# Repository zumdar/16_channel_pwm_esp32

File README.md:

# 16 Channel PWM led dimming board for ESP32

this repo contains the files for a 16 channel pcb to dim LEDS. 

## Description

I designed this board originally for my friend [Eddie Farr](https://www.instagram.com/freaughouse/?hl=en) for an led sculpture he is working on. I've also wanted something like this for a while to dim analog LED strips easily via WLED or ArtNet, or just plain old locally from a microcontroller.

It is designed to take in voltages from 5 to 37 Volts to power the ESP32. That way you can use this with 12 or 24 volt LEDs and dont have to deal with an extra 5V power supply to power the esp32. 

There are two separate places to put power in. 
EITHER plug 5V into the 5V side, or plug 7 - 37V into the other side. 
## pinout

LED1 = GPIO 5

LED2 = GPIO 12

LED3 = GPIO 13

LED4 = GPIO 14

LED5 = GPIO 15

LED6 = GPIO 16

LED7 = GPIO 17

LED8 = GPIO 18

LED9 = GPIO 19

LED10 = GPIO 21

LED11 = GPIO 22

LED12 = GPIO 23

LED13 = GPIO 25

LED14 = GPIO 26

LED15 = GPIO 27

LED16 = GPIO 32
## Schematic 
Rev 3

Rev 1 

## PCB

Rev. 3 - pcb with larger transistors and larger connectors:

Rev. 1 - pcb with larger transistors:

Rev. 1 - pcb with smaller transistors:

## Parts references
### Connectors
- On version 1.3 we are trying out some Molex Microfit connectors
- Crimping tool - [Engineer PA09](https://www.amazon.com/ENGINEER-AWG32-AWG20-Connectors-Oil-Resistant-PA-09/dp/B002AVVO7K?th=1) 
- 
### Common parts
- [Mouser Cart](https://www.mouser.com/ProjectManager/ProjectDetail.aspx?AccessID=f114f2123e) for QTY 5 REV2 boards - this is parts not included with the JLCPCB assembly. 

- [Recommended Generic Crimper](https://www.amazon.com/ENGINEER-AWG32-AWG20-Connectors-Oil-Resistant-PA-09/dp/B002AVVO7K) for Molex Microfit Connectors

- using ESP-WROOM-32 dev board. 2.05" x 1.18" like the kind [found here](https://www.amazon.com/ESP-WROOM-32-Development-Microcontroller-Integrated-Compatible/dp/B0BK13HWBJ/ref=sr_1_4?keywords=esp32&qid=1679947379&sr=8-4&th=1)
- Both pcbs mount with M3 screws
- board has two places for power. one for 5V and one for 8V - 40V. The two connectors MSTBV/MSTBA Phoenix Type, 5.08 pitch. 
  - straight receptacle/header: [1747993 (green)](https://www.mouser.com/ProductDetail/Phoenix-Contact/1747993?qs=cq3Rj917t3li0%2FrJTXaRgg%3D%3D) or [1836561 (orange)](https://www.mouser.com/ProductDetail/Phoenix-Contact/1836561?qs=RahONj4mt5imYCprRrL9IA%3D%3D) or [1740893 (black)](https://www.mouser.com/ProductDetail/Phoenix-Contact/1740893?qs=o3rrLWFGhRnNm6PoJeAVCw%3D%3D)
  - right angle receptacle/header: [1736036 (green)](https://www.mouser.com/ProductDetail/Phoenix-Contact/1736036?qs=IGPQaF7TU6v9VVAvkUDQlA%3D%3D) or [1702878 (white)](https://www.mouser.com/ProductDetail/Phoenix-Contact/1702878?qs=2WS7V4AoKFqZwxKPPB6GZw%3D%3D) or [1876848 (orange)](https://www.mouser.com/ProductDetail/Phoenix-Contact/1876848?qs=KDxjV83btlSGzDlv5NRfLA%3D%3D)
  - terminal block plug: [Wurth 691351500002](https://www.mouser.com/ProductDetail/Wurth-Elektronik/691351500002?qs=7gQLVZk5cPkg%2FrpRGyiXgA%3D%3D) or [Kobiconn 158-P022ESDVP-E](https://www.mouser.com/ProductDetail/Kobiconn/158-P022ESDVP-E?qs=EibfsPFbZarDIylQPyTRxA%3D%3D) or [Amphenol TJ0251530000G](https://www.mouser.com/ProductDetail/Amphenol-Anytek/TJ0251530000G?qs=Mv7BduZupUjx%252Becl1KCPZg%3D%3D)
### larger pcb
- Enclosure mounts with #8 wood screws
-  the larger board uses 3.81mm pitch connector for led outputs
   - 16 channel plug -  pluggable screw terminal block - [TBP02P1-381-16BE](https://www.mouser.com/ProductDetail/490-TBP02P1-381-16BE) 
   - screw terminal receptacle/header 
[TBP02R1-381-16BE](https://www.mouser.com/ProductDetail/490-TBP02R1-381-16BE)
### smaller pcb
- smaller board uses 2.54mm connector for led outputs

## Help

Any advise for common problems or issues.

## Authors

[william kennedy](https://freakylamps.com/)

## Version History

* 1.0
    * Initial Release - March 15, 2023
* 1.1
    * new design with larger TO-252 package for NMOS - March 20, 2023
* 1.2 - april 5, 2023
  * v2 of smaller board. v1 had NMOS pinout wrong
* Rev 3 - May 22, 2024
  * large boards are now larger, using MicroFit connectors for the led outputs, terminal block for PSU inputs
  * switch is on front now
  * Q17 had pinout wrong

## License

This project is licensed under the [NAME HERE] License - see the LICENSE.md file for details

## Acknowledgments

Inspiration comes from [quinLED's analog boards](https://quinled.info/quinled-an-quad/)

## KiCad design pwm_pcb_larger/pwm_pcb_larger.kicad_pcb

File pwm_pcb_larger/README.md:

# 16 Channel PWM led dimming board for ESP32 - larger version with TO252 package

this repo contains the files for a 16 channel pcb to dim leds using TO-252 NMOS package for more current. 

## use case 
- WLED to dim analog LED strips
- ArtNet dmx over wifi to the ESP32 to control 16 channels of led wirelessly

## Author

[william kennedy](https://freakylamps.com/)

## Version History

* 1.1
    * Initial Release - March 20, 2023

## License

This project is licensed under the [NAME HERE] License - see the LICENSE.md file for details

## Acknowledgments

Inspiration comes from [quinLED's analog boards](https://quinled.info/quinled-an-quad/)

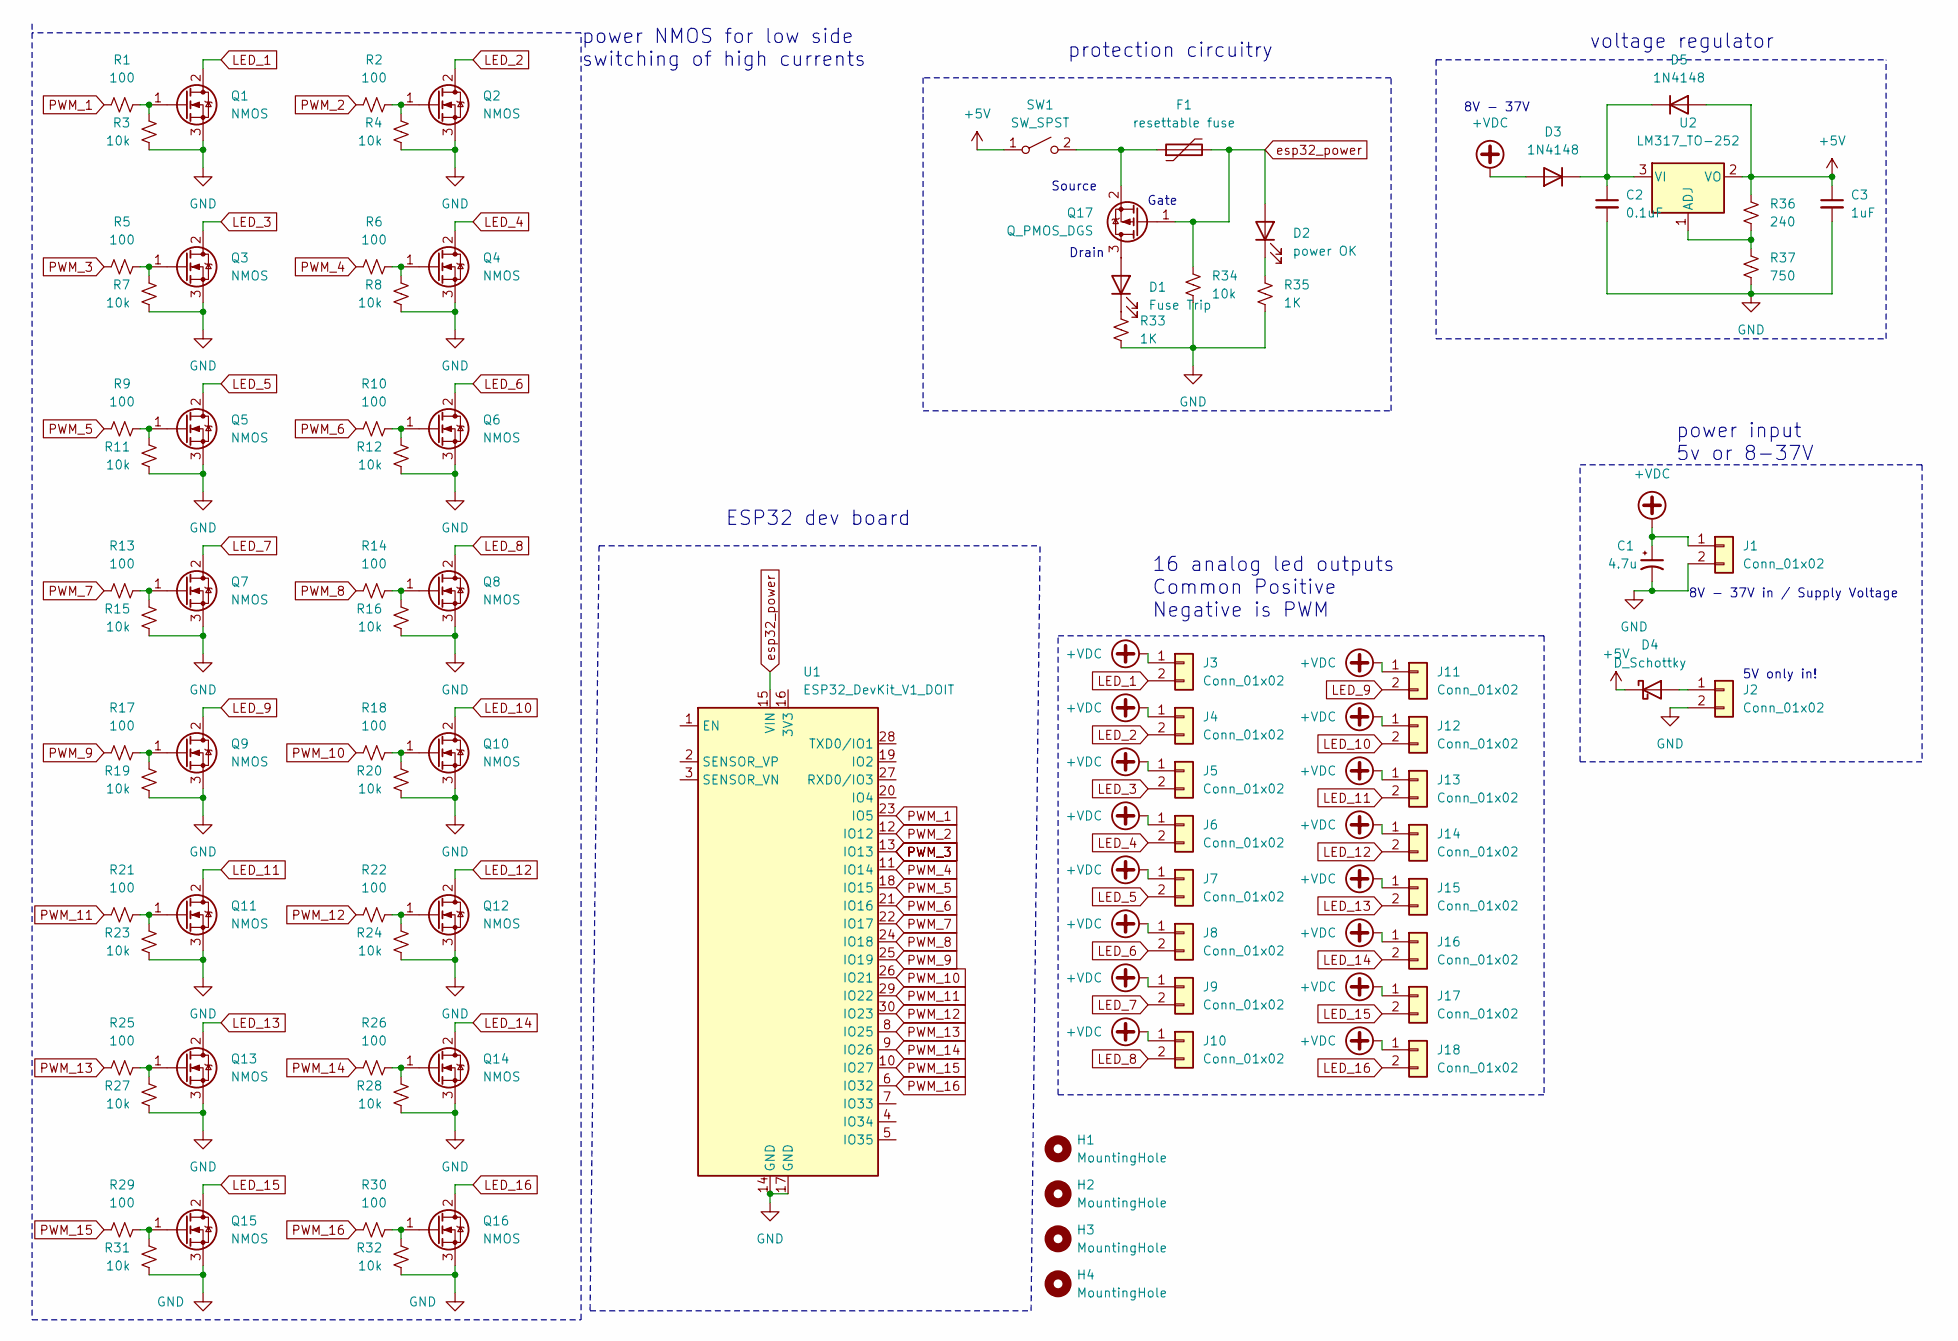
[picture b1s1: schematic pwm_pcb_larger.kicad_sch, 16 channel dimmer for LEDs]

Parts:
C1: 4.7u; C_1206_3216Metric_Pad1.33x1.80mm_HandSolder; LCSC C29823
C2: 0.1uF; C_1206_3216Metric_Pad1.33x1.80mm_HandSolder; LCSC C24497
C3: 1uF; C_1206_3216Metric_Pad1.33x1.80mm_HandSolder; LCSC C1848
D1: Fuse Trip; LED_0805_2012Metric; LCSC C84256
D2: power OK; LED_0805_2012Metric; LCSC C34499
D3, D5: 1N4148; D_SOD-323; LCSC C2128
D4: D_Schottky; D_SMA; LCSC C2480
F1: resettable fuse; Fuse_1206_3216Metric; LCSC C70077
H1, H2, H3, H4: MountingHole; MountingHole_3.2mm_M3
J1, J2: Conn_01x02; Kobiconn - 2 pin terminal - 158P02DT39BE
J3, J4, J5, J6, J7, J8, J9, J10, J11, J12, J13, J14, J15, J16, J17, J18: Conn_01x02; Molex_Micro-Fit_3.0_43045-0212_2x01_P3.00mm_Vertical
Q1, Q2, Q3, Q4, Q5, Q6, Q7, Q8, Q9, Q10, Q11, Q12, Q13, Q14, Q15, Q16: NMOS; TO-252-2; LCSC C2995345
Q17: Q_PMOS_DGS; SOT-23; LCSC C15127
R1, R2, R5, R6, R9, R10, R13, R14, R17, R18, R21, R22, R25, R26, R29, R30: 100; R_0805_2012Metric; LCSC C17408
R3, R4, R7, R8, R11, R12, R15, R16, R19, R20, R23, R24, R27, R28, R31, R32, R34: 10k; R_0805_2012Metric; LCSC C17414
R33, R35: 1K; R_0805_2012Metric; LCSC C17513
R36: 240; R_0805_2012Metric; LCSC C17572
R37: 750; R_0805_2012Metric; LCSC C17818
SW1: SW_SPST; SW_SPST_CK_RS282G05A3; LCSC C54948
U1: ESP32_DevKit_V1_DOIT; esp32_devkit_v1_doit
U2: LM317_TO-252; TO-252-2; LCSC C75510

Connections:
+5V: C3.1, D4.1 (K), D5.2 (A), R36.1, SW1.1 (A), U2.2 (VO)
+VDC: C1.1, D3.2 (A), J1.1, J3.1, J4.1, J5.1, J6.1, J7.1, J8.1, J9.1, J10.1, J11.1, J12.1, J13.1, J14.1, J15.1, J16.1, J17.1, J18.1
GND: C1.2, C2.2, C3.2, J1.2, J2.2, Q1.3 (S), Q2.3 (S), Q3.3 (S), Q4.3 (S), Q5.3 (S), Q6.3 (S), Q7.3 (S), Q8.3 (S), Q9.3 (S), Q10.3 (S), Q11.3 (S), Q12.3 (S), Q13.3 (S), Q14.3 (S), Q15.3 (S), Q16.3 (S), R3.1, R4.1, R7.1, R8.1, R11.1, R12.1, R15.1, R16.1, R19.1, R20.1, R23.1, R24.1, R27.1, R28.1, R31.1, R32.1, R33.1, R34.1, R35.1, R37.2, U1.14 (GND), U1.17 (GND)
LED_1: J3.2, Q1.2 (D)
LED_2: J4.2, Q2.2 (D)
LED_3: J5.2, Q3.2 (D)
LED_4: J6.2, Q4.2 (D)
LED_5: J7.2, Q5.2 (D)
LED_6: J8.2, Q6.2 (D)
LED_7: J9.2, Q7.2 (D)
LED_8: J10.2, Q8.2 (D)
LED_9: J11.2, Q9.2 (D)
LED_10: J12.2, Q10.2 (D)
LED_11: J13.2, Q11.2 (D)
LED_12: J14.2, Q12.2 (D)
LED_13: J15.2, Q13.2 (D)
LED_14: J16.2, Q14.2 (D)
LED_15: J17.2, Q15.2 (D)
LED_16: J18.2, Q16.2 (D)
unnamed: D1.2 (A), Q17.3 (D)
unnamed: D1.1 (K), R33.2
unnamed: D2.1 (K), R35.2
unnamed: C2.1, D3.1 (K), D5.1 (K), U2.3 (VI)
unnamed: D4.2 (A), J2.1
unnamed: Q1.1 (G), R1.2, R3.2
unnamed: Q2.1 (G), R2.2, R4.2
unnamed: Q3.1 (G), R5.2, R7.2
unnamed: Q4.1 (G), R6.2, R8.2
unnamed: Q5.1 (G), R9.2, R11.2
unnamed: Q6.1 (G), R10.2, R12.2
unnamed: Q7.1 (G), R13.2, R15.2
unnamed: Q8.1 (G), R14.2, R16.2
unnamed: Q9.1 (G), R17.2, R19.2
unnamed: Q10.1 (G), R18.2, R20.2
unnamed: Q11.1 (G), R21.2, R23.2
unnamed: Q12.1 (G), R22.2, R24.2
unnamed: Q13.1 (G), R25.2, R27.2
unnamed: Q14.1 (G), R26.2, R28.2
unnamed: Q15.1 (G), R29.2, R31.2
unnamed: Q16.1 (G), R30.2, R32.2
unnamed: F1.1, Q17.2 (S), SW1.2 (B)
unnamed: R36.2, R37.1, U2.1 (ADJ)
PWM_1: R1.1, U1.23 (IO5)
PWM_2: R2.1, U1.12 (IO12)
PWM_3: R5.1, U1.13 (IO13)
PWM_4: R6.1, U1.11 (IO14)
PWM_5: R9.1, U1.18 (IO15)
PWM_6: R10.1, U1.21 (IO16)
PWM_7: R13.1, U1.22 (IO17)
PWM_8: R14.1, U1.24 (IO18)
PWM_9: R17.1, U1.25 (IO19)
PWM_10: R18.1, U1.26 (IO21)
PWM_11: R21.1, U1.29 (IO22)
PWM_12: R22.1, U1.30 (IO23)
PWM_13: R25.1, U1.8 (IO25)
PWM_14: R26.1, U1.9 (IO26)
PWM_15: R29.1, U1.10 (IO27)
PWM_16: R30.1, U1.6 (IO32)
esp32_power: D2.2 (A), F1.2, Q17.1 (G), R34.2, U1.15 (VIN)

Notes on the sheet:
5V only in!
power NMOS for low side switching of high currents
ESP32 dev board
Source
Drain
8V - 37V
8V - 37V in / Supply Voltage
power input 5v or 8-37V
Gate
protection circuitry
voltage regulator
16 analog led outputs Common Positive Negative is PWM

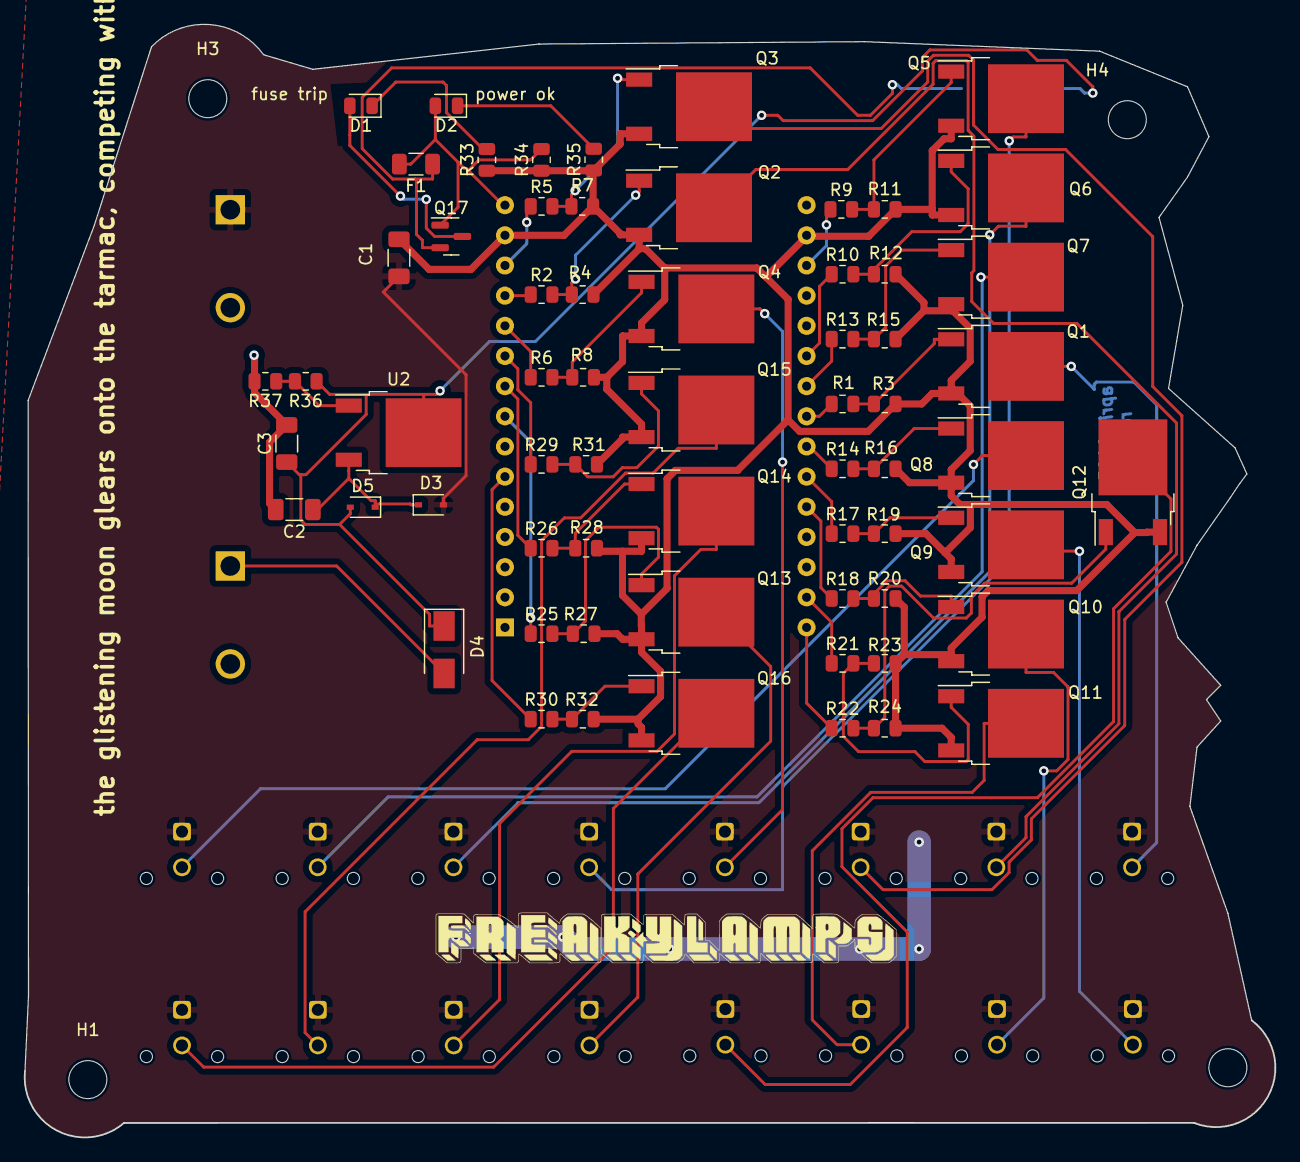
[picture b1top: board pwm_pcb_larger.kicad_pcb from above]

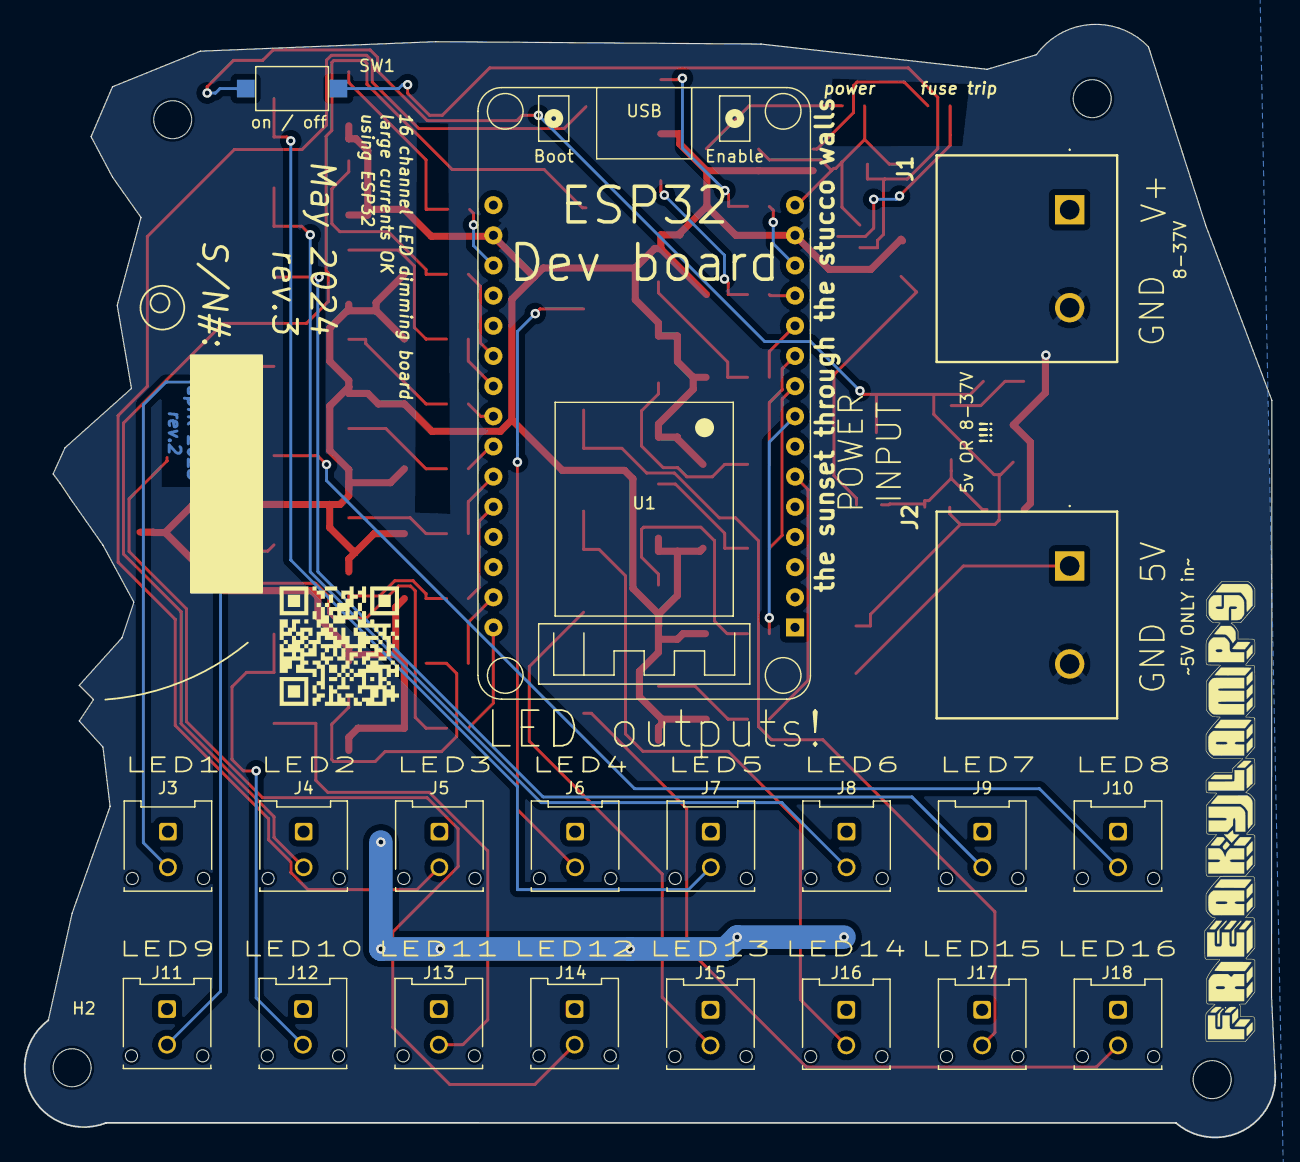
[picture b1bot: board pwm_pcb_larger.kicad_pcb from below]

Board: 2 copper layers, 105.3 x 93.7 mm, 89 parts (21 on the bottom side), 59 nets.

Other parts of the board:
G1: LOGO; 16_channel_pcb

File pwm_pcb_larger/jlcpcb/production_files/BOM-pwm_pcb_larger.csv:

Comment,Designator,Footprint,LCSC
Q_PMOS_DGS,Q17,SOT-23,C15127
100,"R1,R10,R13,R14,R17,R18,R2,R21,R22,R25,R26,R29,R30,R5,R6,R9",R_0805_2012Metric,C17408
10k,"R11,R12,R15,R16,R19,R20,R23,R24,R27,R28,R3,R31,R32,R34,R4,R7,R8",R_0805_2012Metric,C17414
1K,"R33,R35",R_0805_2012Metric,C17513
240,R36,R_0805_2012Metric,C17572
750,R37,R_0805_2012Metric,C17818
1uF,C3,C_1206_3216Metric_Pad1.33x1.80mm_HandSolder,C1848
1N4148,"D3,D5",D_SOD-323,C2128
0.1uF,C2,C_1206_3216Metric_Pad1.33x1.80mm_HandSolder,C24497
D_Schottky,D4,D_SMA,C2480
4.7u,C1,C_1206_3216Metric_Pad1.33x1.80mm_HandSolder,C29823
NMOS,"Q1,Q10,Q11,Q12,Q13,Q14,Q15,Q16,Q2,Q3,Q4,Q5,Q6,Q7,Q8,Q9",TO-252-2,C2995345
power OK,D2,LED_0805_2012Metric,C34499
SW_SPST,SW1,SW_SPST_CK_RS282G05A3,C54948
resettable fuse,F1,Fuse_1206_3216Metric,C70077
LM317_TO-252,U2,TO-252-2,C75510
Fuse Trip,D1,LED_0805_2012Metric,C84256
Conn_01x02,J3,Molex_Micro-Fit_3.0_43045-0212_2x01_P3.00mm_Vertical,
Conn_01x02,J2,Kobiconn - 2 pin terminal - 158P02DT39BE,
Conn_01x02,J1,Kobiconn - 2 pin terminal - 158P02DT39BE,
ESP32_DevKit_V1_DOIT,U1,esp32_devkit_v1_doit,
Conn_01x02,J9,Molex_Micro-Fit_3.0_43045-0212_2x01_P3.00mm_Vertical,
Conn_01x02,J13,Molex_Micro-Fit_3.0_43045-0212_2x01_P3.00mm_Vertical,
Conn_01x02,J4,Molex_Micro-Fit_3.0_43045-0212_2x01_P3.00mm_Vertical,
Conn_01x02,J15,Molex_Micro-Fit_3.0_43045-0212_2x01_P3.00mm_Vertical,
Conn_01x02,J6,Molex_Micro-Fit_3.0_43045-0212_2x01_P3.00mm_Vertical,
Conn_01x02,J11,Molex_Micro-Fit_3.0_43045-0212_2x01_P3.00mm_Vertical,
Conn_01x02,J17,Molex_Micro-Fit_3.0_43045-0212_2x01_P3.00mm_Vertical,
Conn_01x02,J14,Molex_Micro-Fit_3.0_43045-0212_2x01_P3.00mm_Vertical,
Conn_01x02,J12,Molex_Micro-Fit_3.0_43045-0212_2x01_P3.00mm_Vertical,
Conn_01x02,J8,Molex_Micro-Fit_3.0_43045-0212_2x01_P3.00mm_Vertical,
Conn_01x02,J7,Molex_Micro-Fit_3.0_43045-0212_2x01_P3.00mm_Vertical,
Conn_01x02,J10,Molex_Micro-Fit_3.0_43045-0212_2x01_P3.00mm_Vertical,
Conn_01x02,J18,Molex_Micro-Fit_3.0_43045-0212_2x01_P3.00mm_Vertical,
Conn_01x02,J16,Molex_Micro-Fit_3.0_43045-0212_2x01_P3.00mm_Vertical,
Conn_01x02,J5,Molex_Micro-Fit_3.0_43045-0212_2x01_P3.00mm_Vertical,

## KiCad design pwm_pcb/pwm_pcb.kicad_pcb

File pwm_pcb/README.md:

# 16 Channel PWM led dimming board for ESP32

this repo contains the files for a 16 channel pcb to dim leds. 

## Description

An in-depth paragraph about your project and overview of use.

## Getting Started

## Help

Any advise for common problems or issues.

## Authors

[william kennedy](https://freakylamps.com/)

## Version History

* 1.0
    * Initial Release - March 15, 2023

## License

This project is licensed under the [NAME HERE] License - see the LICENSE.md file for details

## Acknowledgments

Inspiration, code snippets, etc.

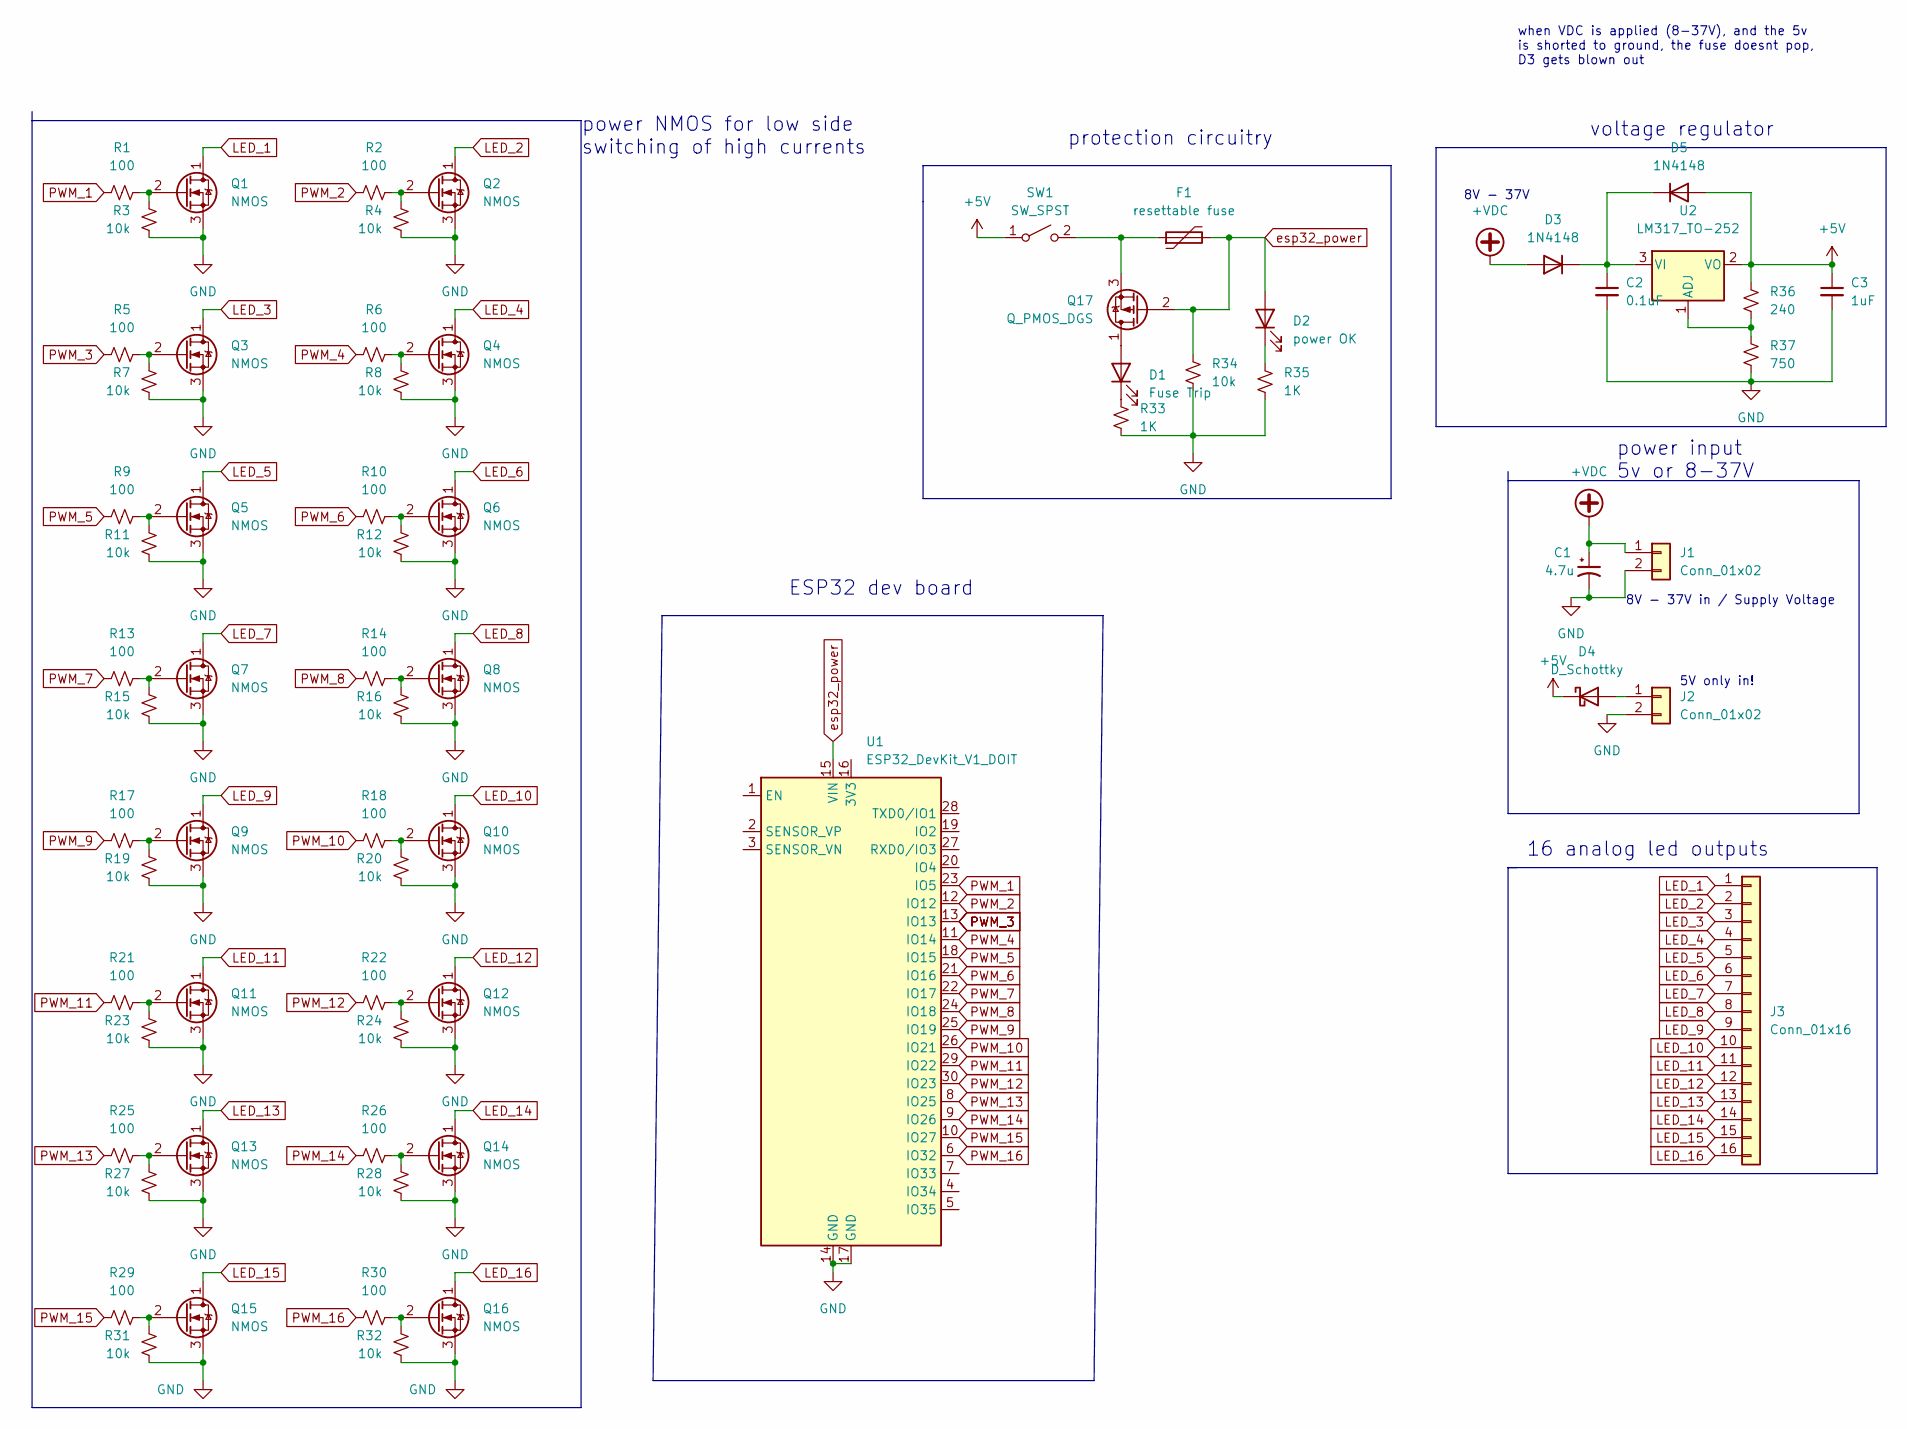
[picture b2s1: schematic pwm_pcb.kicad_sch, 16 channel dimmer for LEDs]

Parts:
C1: 4.7u; C_1206_3216Metric_Pad1.33x1.80mm_HandSolder; LCSC C29823
C2: 0.1uF; C_1206_3216Metric_Pad1.33x1.80mm_HandSolder; LCSC C24497
C3: 1uF; C_1206_3216Metric_Pad1.33x1.80mm_HandSolder; LCSC C1848
D1: Fuse Trip; LED_1206_3216Metric; LCSC C84256
D2: power OK; LED_1206_3216Metric; LCSC C2297
D3, D5: 1N4148; D_SOD-323; LCSC C2128
D4: D_Schottky; D_SMA; LCSC C2480
F1: resettable fuse; Fuse_1206_3216Metric; LCSC C192524
J1, J2: Conn_01x02; PhoenixContact_MSTBVA_2,5_2-G-5,08_1x02_P5.08mm_Vertical
J3: Conn_01x16; PinHeader_1x16_P2.54mm_Vertical
Q1, Q2, Q3, Q4, Q5, Q6, Q7, Q8, Q9, Q10, Q11, Q12, Q13, Q14, Q15, Q16: NMOS; SOT-23; LCSC C20917
Q17: Q_PMOS_DGS; SOT-23; LCSC C15127
R1, R2, R5, R6, R9, R10, R13, R14, R17, R18, R21, R22, R25, R26, R29, R30: 100; R_0805_2012Metric; LCSC C17408
R3, R4, R7, R8, R11, R12, R15, R16, R19, R20, R23, R24, R27, R28, R31, R32, R34: 10k; R_0805_2012Metric; LCSC C17414
R33, R35: 1K; R_0805_2012Metric; LCSC C17513
R36: 240; R_0805_2012Metric; LCSC C17572
R37: 750; R_0805_2012Metric; LCSC C17818
SW1: SW_SPST; SW_SPST_CK_RS282G05A3; LCSC C54948
U1: ESP32_DevKit_V1_DOIT; esp32_devkit_v1_doit
U2: LM317_TO-252; TO-252-2; LCSC C75510

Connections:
+5V: C3.1, D4.1 (K), D5.2 (A), R36.1, SW1.1 (A), U2.2 (VO)
+VDC: C1.1, D3.2 (A), J1.1
GND: C1.2, C2.2, C3.2, J1.2, J2.2, Q1.3 (S), Q2.3 (S), Q3.3 (S), Q4.3 (S), Q5.3 (S), Q6.3 (S), Q7.3 (S), Q8.3 (S), Q9.3 (S), Q10.3 (S), Q11.3 (S), Q12.3 (S), Q13.3 (S), Q14.3 (S), Q15.3 (S), Q16.3 (S), R3.1, R4.1, R7.1, R8.1, R11.1, R12.1, R15.1, R16.1, R19.1, R20.1, R23.1, R24.1, R27.1, R28.1, R31.1, R32.1, R33.1, R34.1, R35.1, R37.2, U1.14 (GND), U1.17 (GND)
LED_1: J3.1, Q1.1 (D)
LED_2: J3.2, Q2.1 (D)
LED_3: J3.3, Q3.1 (D)
LED_4: J3.4, Q4.1 (D)
LED_5: J3.5, Q5.1 (D)
LED_6: J3.6, Q6.1 (D)
LED_7: J3.7, Q7.1 (D)
LED_8: J3.8, Q8.1 (D)
LED_9: J3.9, Q9.1 (D)
LED_10: J3.10, Q10.1 (D)
LED_11: J3.11, Q11.1 (D)
LED_12: J3.12, Q12.1 (D)
LED_13: J3.13, Q13.1 (D)
LED_14: J3.14, Q14.1 (D)
LED_15: J3.15, Q15.1 (D)
LED_16: J3.16, Q16.1 (D)
unnamed: C2.1, D3.1 (K), D5.1 (K), U2.3 (VI)
unnamed: D1.1 (K), R33.2
unnamed: D1.2 (A), Q17.1 (D)
unnamed: D2.1 (K), R35.2
unnamed: D4.2 (A), J2.1
unnamed: F1.1, Q17.3 (S), SW1.2 (B)
unnamed: Q1.2 (G), R1.2, R3.2
unnamed: Q2.2 (G), R2.2, R4.2
unnamed: Q3.2 (G), R5.2, R7.2
unnamed: Q4.2 (G), R6.2, R8.2
unnamed: Q5.2 (G), R9.2, R11.2
unnamed: Q6.2 (G), R10.2, R12.2
unnamed: Q7.2 (G), R13.2, R15.2
unnamed: Q8.2 (G), R14.2, R16.2
unnamed: Q9.2 (G), R17.2, R19.2
unnamed: Q10.2 (G), R18.2, R20.2
unnamed: Q11.2 (G), R21.2, R23.2
unnamed: Q12.2 (G), R22.2, R24.2
unnamed: Q13.2 (G), R25.2, R27.2
unnamed: Q14.2 (G), R26.2, R28.2
unnamed: Q15.2 (G), R29.2, R31.2
unnamed: Q16.2 (G), R30.2, R32.2
unnamed: R36.2, R37.1, U2.1 (ADJ)
PWM_1: R1.1, U1.23 (IO5)
PWM_2: R2.1, U1.12 (IO12)
PWM_3: R5.1, U1.13 (IO13)
PWM_4: R6.1, U1.11 (IO14)
PWM_5: R9.1, U1.18 (IO15)
PWM_6: R10.1, U1.21 (IO16)
PWM_7: R13.1, U1.22 (IO17)
PWM_8: R14.1, U1.24 (IO18)
PWM_9: R17.1, U1.25 (IO19)
PWM_10: R18.1, U1.26 (IO21)
PWM_11: R21.1, U1.29 (IO22)
PWM_12: R22.1, U1.30 (IO23)
PWM_13: R25.1, U1.8 (IO25)
PWM_14: R26.1, U1.9 (IO26)
PWM_15: R29.1, U1.10 (IO27)
PWM_16: R30.1, U1.6 (IO32)
esp32_power: D2.2 (A), F1.2, Q17.2 (G), R34.2, U1.15 (VIN)

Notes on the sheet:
when VDC is applied (8-37V), and the 5v is shorted to ground, the fuse doesnt pop, D3 gets blown out
5V only in!
power NMOS for low side switching of high currents
ESP32 dev board
8V - 37V
8V - 37V in / Supply Voltage
power input 5v or 8-37V
protection circuitry
voltage regulator
16 analog led outputs

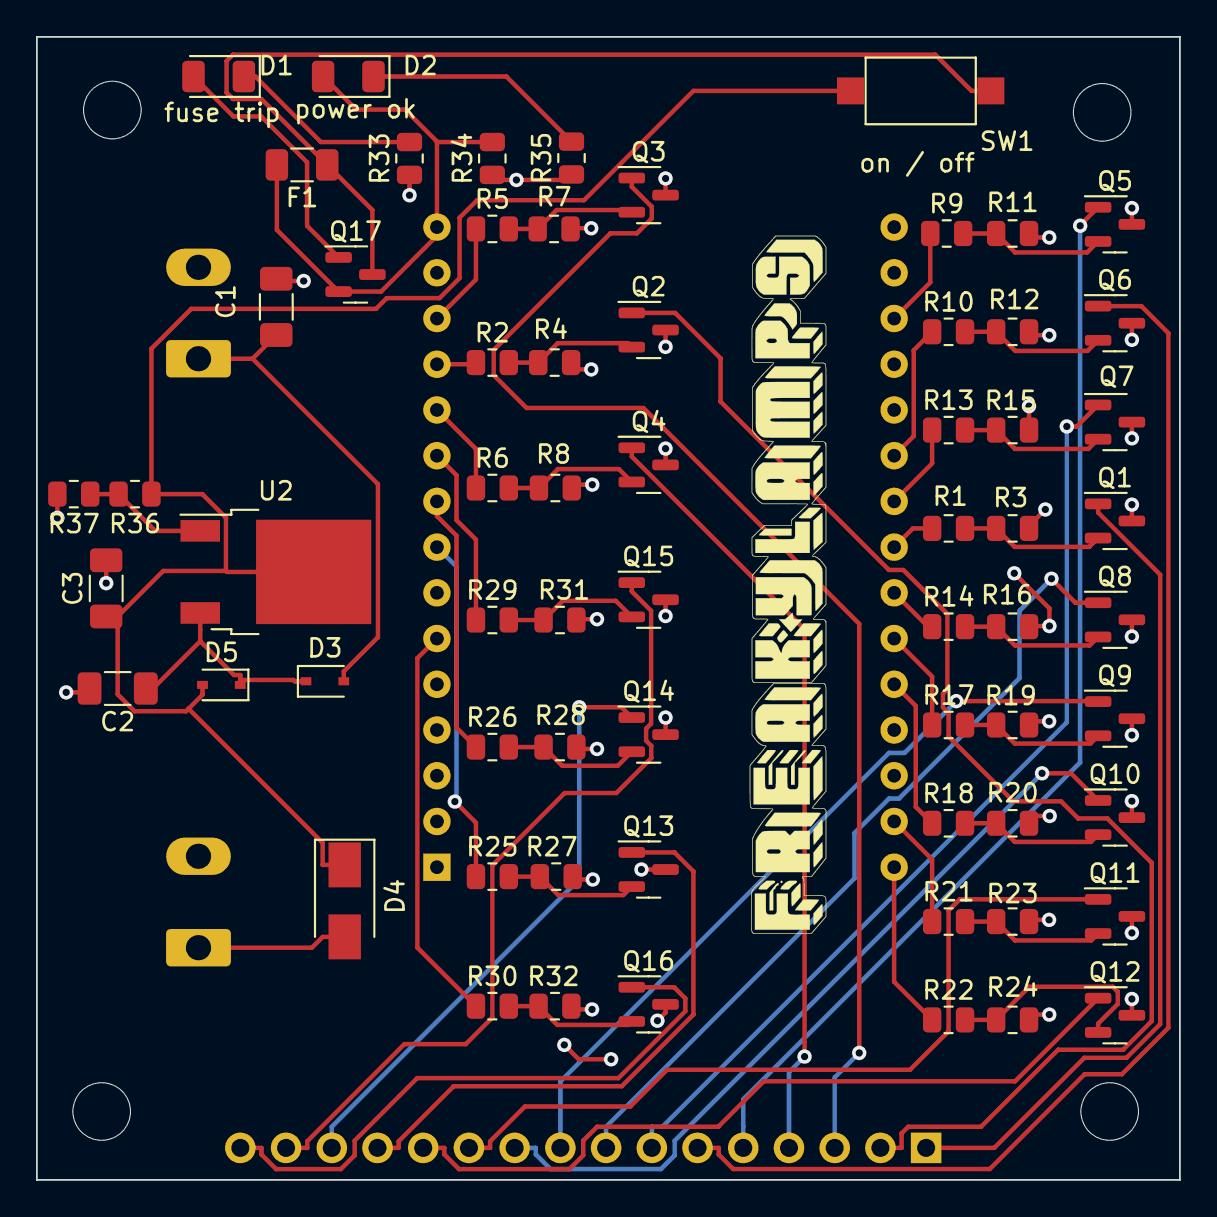
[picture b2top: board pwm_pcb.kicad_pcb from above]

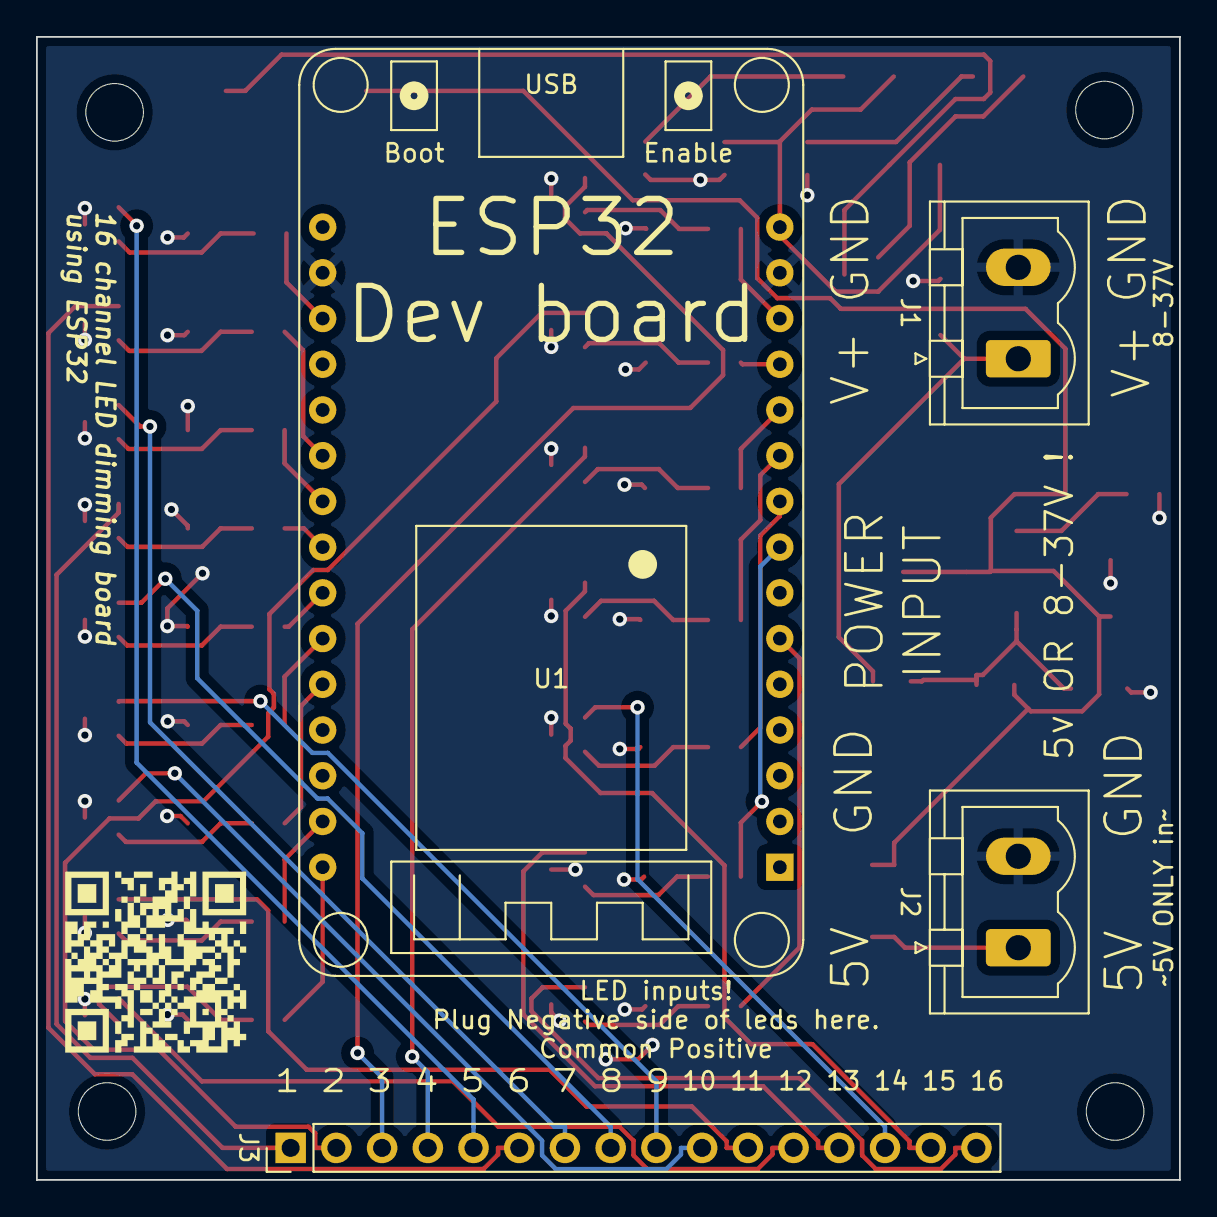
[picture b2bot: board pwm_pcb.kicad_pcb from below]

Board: 2 copper layers, 63.5 x 63.5 mm, 74 parts (5 on the bottom side), 59 nets.

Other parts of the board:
G1: LOGO; 16_channel_pcb
MH1, MH2, MH3, MH4: MountingHole_3.2mm_M3

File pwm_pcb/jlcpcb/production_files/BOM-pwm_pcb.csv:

Comment,Designator,Footprint,LCSC
Q_PMOS_DGS,Q17,SOT-23,C15127
100,"R1,R10,R13,R14,R17,R18,R2,R21,R22,R25,R26,R29,R30,R5,R6,R9",R_0805_2012Metric,C17408
10k,"R11,R12,R15,R16,R19,R20,R23,R24,R27,R28,R3,R31,R32,R34,R4,R7,R8",R_0805_2012Metric,C17414
1K,"R33,R35",R_0805_2012Metric,C17513
240,R36,R_0805_2012Metric,C17572
750,R37,R_0805_2012Metric,C17818
1uF,C3,C_1206_3216Metric_Pad1.33x1.80mm_HandSolder,C1848
NMOS,"Q1,Q10,Q11,Q12,Q13,Q14,Q15,Q16,Q2,Q3,Q4,Q5,Q6,Q7,Q8,Q9",SOT-23,C20917
1N4148,"D3,D5",D_SOD-323,C2128
power OK,D2,LED_1206_3216Metric,C2297
0.1uF,C2,C_1206_3216Metric_Pad1.33x1.80mm_HandSolder,C24497
D_Schottky,D4,D_SMA,C2480
4.7u,C1,C_1206_3216Metric_Pad1.33x1.80mm_HandSolder,C29823
SW_SPST,SW1,SW_SPST_CK_RS282G05A3,C54948
Polyfuse,F1,Fuse_1206_3216Metric,C70077
LM317_TO-252,U2,TO-252-2,C75510
Fuse Trip,D1,LED_1206_3216Metric,C84256
Conn_01x16,J3,PinHeader_1x16_P2.54mm_Vertical,
Conn_01x02,J2,"PhoenixContact_MSTBVA_2,5_2-G-5,08_1x02_P5.08mm_Vertical",
Conn_01x02,J1,"PhoenixContact_MSTBVA_2,5_2-G-5,08_1x02_P5.08mm_Vertical",
ESP32_DevKit_V1_DOIT,U1,esp32_devkit_v1_doit,

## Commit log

2023-03-15 adding a readme
2023-03-20 adding larger pcb
2023-03-20 updating readmes
2023-03-20 small readme change
2023-03-20 readme update
2023-03-27 adding parts ref to readme
2023-04-03 adding test code and 3d print files
2023-04-06 updating v2 of pcb
2023-04-14 updates to the enclosure file
2023-04-15 adding pinout on readme
2023-04-25 testing
2023-04-25 small change
2024-05-21 starting rev b with new connectors
2024-05-22 updating the new rev board with new connectors for led outputs and PSU input
2024-05-22 rev 3 finished and sent to JLC for fab
2024-05-22 forgot readme
2024-05-23 making BOM
2024-05-23 adding readme BOM stuff
2024-05-30 adding keepout zone to areas that are supposed to be FR4
